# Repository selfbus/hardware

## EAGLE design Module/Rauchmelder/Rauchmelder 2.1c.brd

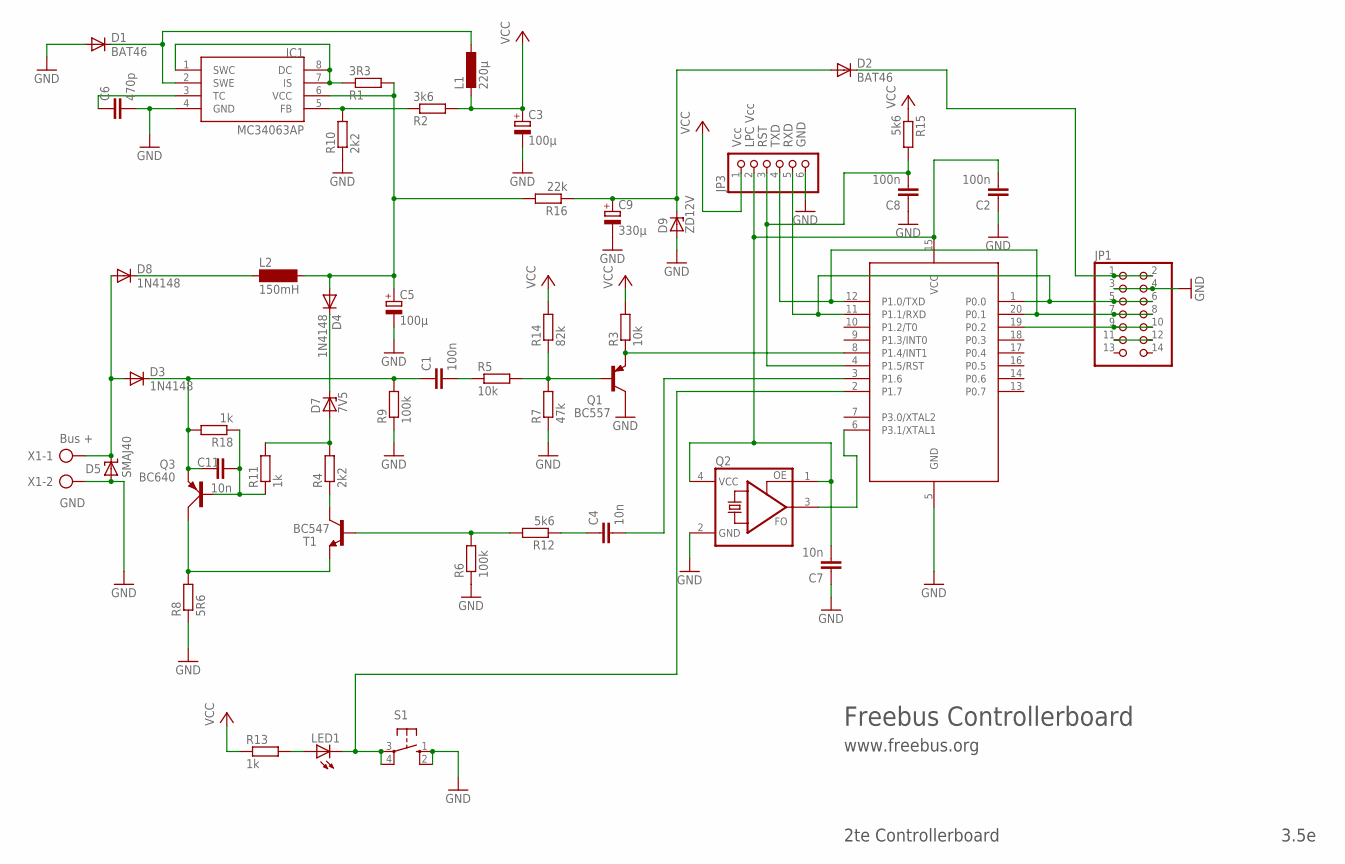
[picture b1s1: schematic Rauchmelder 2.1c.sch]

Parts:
89LPC922: 89LPC922; DIL20
C1, C2, C8: 100n; C025-024X044
C3: 100µ; E2,5-6
C4, C11: 10n; C025-024X044
C5: 100µ; E3,5-8
C6: 470p; C025-024X044
C7: 10n; C1206
C9: 330µ; E3,5-8
D1, D2: BAT46; DO34-7
D3, D4: 1N4148; DO35-10
D5: SMAJ40; SMBJ
D7: 7V5; ZDIO-2.5
D8: 1N4148; D-7.5
D9: ZD12V; DO34Z7
IC1: MC34063AP; DIL08
JP1: PINHD-2X7; 2X07
JP3: PINHD-1X6; 1X06
L1: 220µ; 0207/12
L2: 150mH; BS11
LED1: LED3MM
Q1: BC557; TO92
Q2: ASFL; ASF
Q3: BC640; SOT54D
R1: 3R3; 0207/7
R2: 3k6; 0207/7
R3, R5: 10k; 0207/7
R4: 2k2; 0207/2V
R6: 100k; 0207/2V
R7: 47k; 0207/7
R8: 5R6; 0207/2V
R9: 100k; 0207/7
R10: 2k2; 0207/7
R11, R18: 1k; 0207/2V
R12: 5k6; 0207/7
R13: 1k; 0207/7
R14: 82k; 0207/7
R15: 5k6; 0207/2V
R16: 22k; 0207/2V
S1: 10-XX; B3F-10XX
T1: BC547; TO92
X1: AK500/2

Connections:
EIB+: D3.A, D5.C, D8.A, X1.1
GND: 89LPC922.5 (GND), C2.1, C3.-, C5.-, C6.2, C7.1, C8.1, C9.-, D1.A, D5.A, D9.A, IC1.4 (GND), JP1.3, JP1.4, JP3.6, Q1.3 (C), Q2.2 (GND), R6.1, R7.1, R8.1, R9.1, R10.1, S1.1 (S), S1.2 (S1), X1.2
unnamed: 89LPC922.8 (P1.4/INT1), Q1.1 (E), R3.1
unnamed: Q1.2 (B), R5.2, R7.2, R14.1
unnamed: 89LPC922.6 (P3.1/XTAL1), Q2.3 (FO)
unnamed: C11.2, Q3.B, R11.1, R18.1
unnamed: 89LPC922.3 (P1.6), C4.2
unnamed: 89LPC922.15 (VCC), C2.2, C7.2, JP3.2, Q2.1 (OE), Q2.4 (VCC)
unnamed: 89LPC922.2 (P1.7), LED1.K (C), S1.3, S1.4 (P1)
unnamed: IC1.1 (SWC), IC1.7 (IS), IC1.8 (DC), R1.1
unnamed: LED1.A, R13.2
unnamed: C9.+, D2.A, D9.C, R16.1
unnamed: IC1.5 (FB), R2.1, R10.2
unnamed: D1.C, IC1.2 (SWE), L1.1
unnamed: D8.C, L2.1
unnamed: C6.1, IC1.3 (TC)
unnamed: D4.C, D7.C
unnamed: C1.2, R5.1
unnamed: C5.+, D4.A, IC1.6 (VCC), L2.2, R1.2, R16.2
unnamed: D2.C, JP1.1, JP1.2
unnamed: 89LPC922.4 (P1.5/RST), C8.2, JP3.3, R15.2
unnamed: 89LPC922.19 (P0.2), JP1.9, JP1.10
unnamed: C4.1, R12.1
unnamed: R4.1, T1.3 (C)
unnamed: JP1.11, JP1.12
unnamed: D7.A, R4.2, R11.2
unnamed: Q3.C, R8.2, T1.1 (E)
unnamed: C1.1, C11.1, D3.C, Q3.E, R9.2, R18.2
unnamed: R6.2, R12.2, T1.2 (B)
RX: 89LPC922.1 (P0.0), 89LPC922.11 (P1.1/RXD), JP1.5, JP1.6, JP3.5
TX: 89LPC922.12 (P1.0/TXD), 89LPC922.20 (P0.1), JP1.7, JP1.8, JP3.4
VCC: C3.+, JP3.1, L1.2, R2.2, R3.2, R13.1, R14.2, R15.1

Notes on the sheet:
Bus +
GND
Vcc
LPC Vcc
RST
TXD
RXD
Freebus Controllerboard
www.freebus.org
2te Controllerboard
3.5e

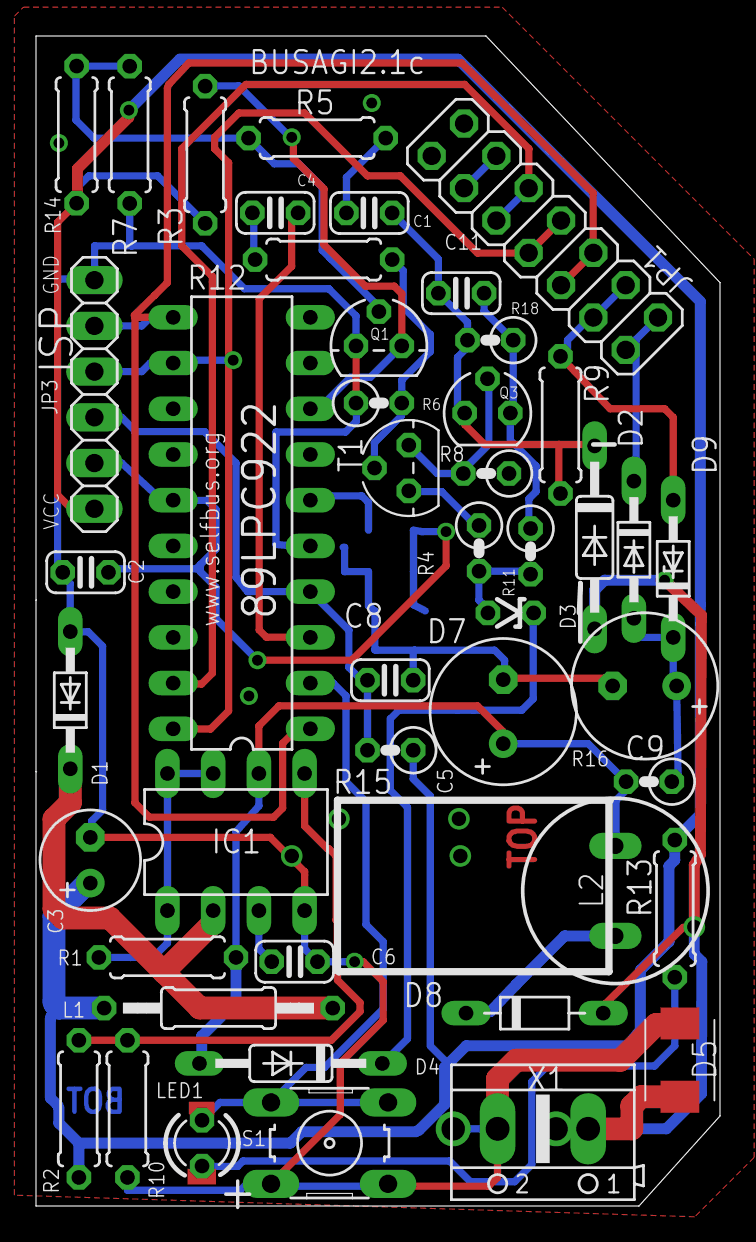
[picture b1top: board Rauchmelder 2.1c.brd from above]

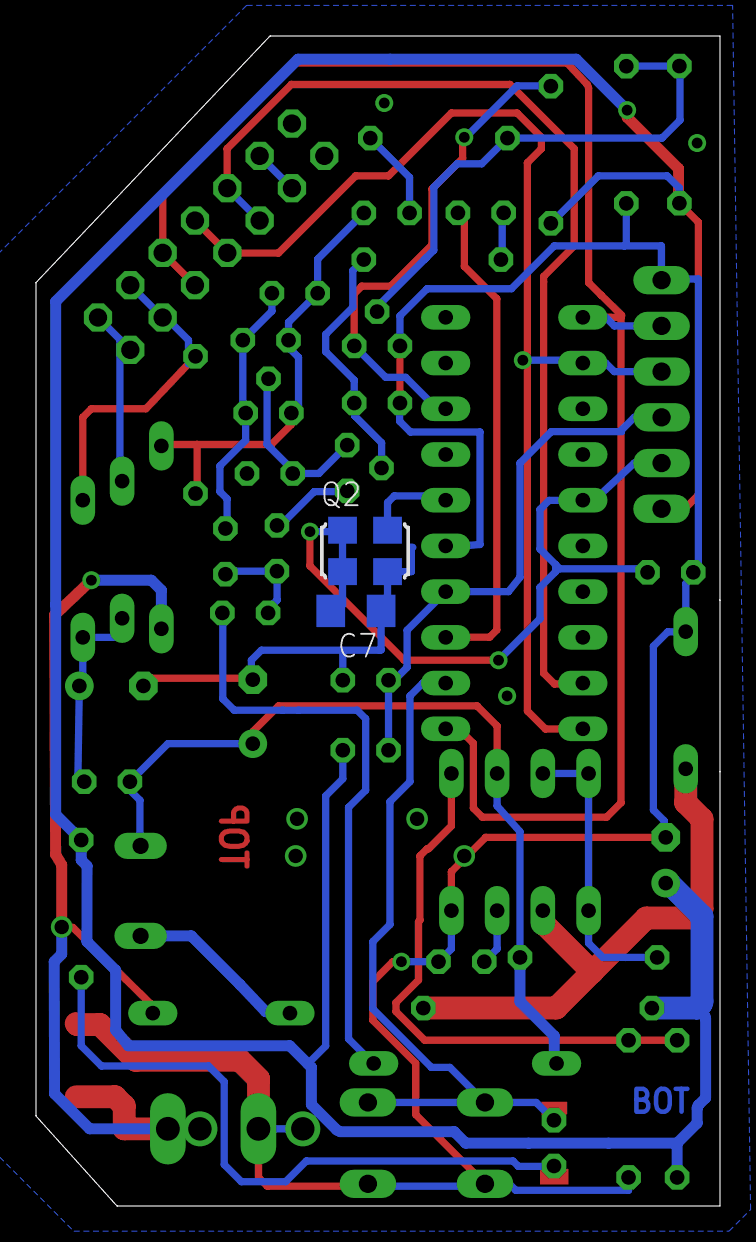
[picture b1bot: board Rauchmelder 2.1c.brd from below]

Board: 2 copper layers, 38.0 x 65.0 mm, 48 parts (2 on the bottom side), 32 nets.

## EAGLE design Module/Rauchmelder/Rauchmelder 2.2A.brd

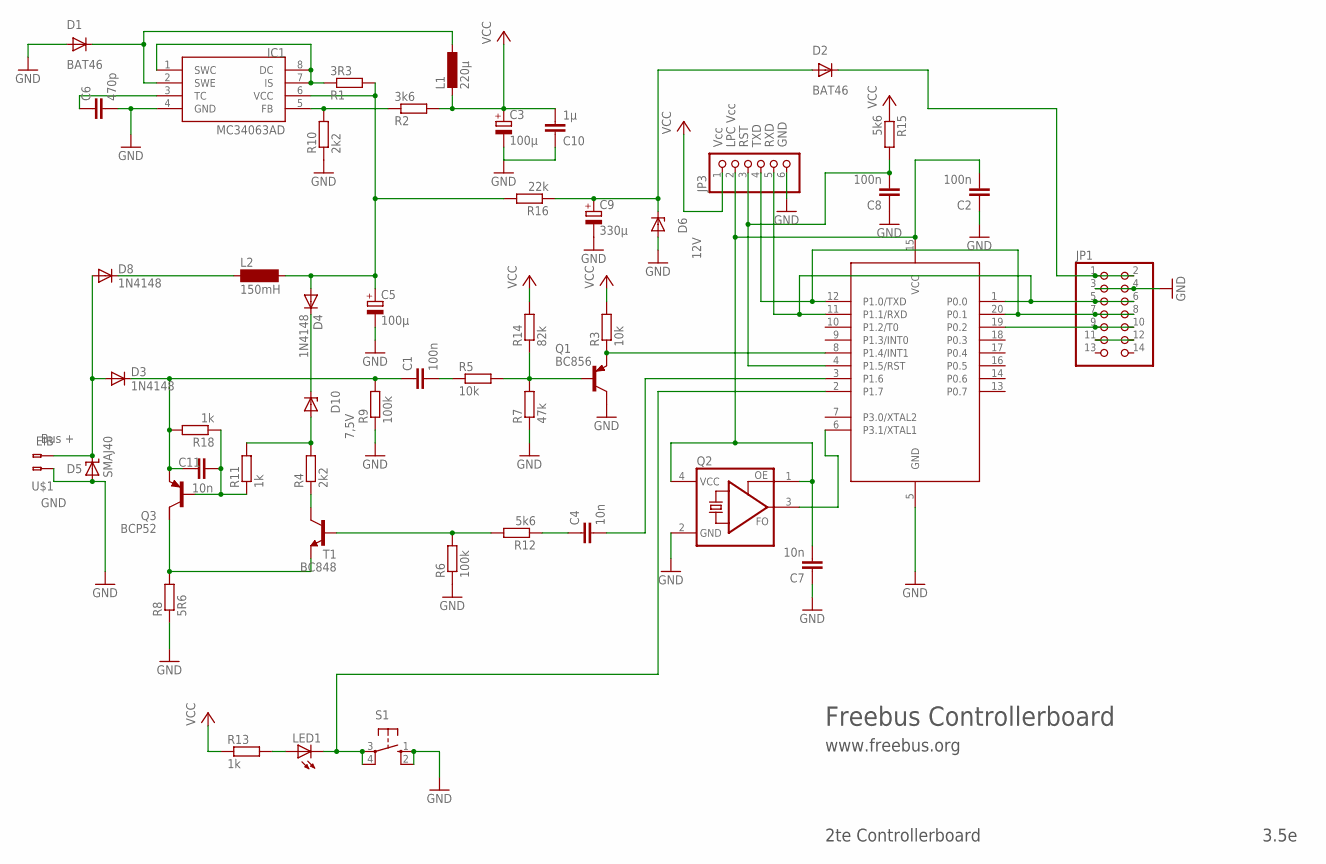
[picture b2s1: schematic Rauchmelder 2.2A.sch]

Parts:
C1, C2, C8: 100n; C1206
C3: 100µ; SANYO-OSCON_SMD_B6
C4, C7, C11: 10n; C1206
C5: 100µ; SANYO-OSCON_SMD_C6
C6: 470p; C1206
C9: 330µ; E3,5-8
C10: 1µ; C1206
D1, D2: BAT46; MINIMELF
D3, D4, D8: 1N4148; MINIMELF
D5: SMAJ40; SMBJ
D6: 12V; MINIMELF
D10: 7,5V; MINIMELF
IC1: MC34063AD; SOIC8
IC3: LPC922FDH; TSSOP20
JP1: PINHD-2X7; 2X07
JP3: PINHD-1X6; 1X06
L1: 220µ; 0207/10
L2: 150mH; BS11
LED1: LED3MM
Q1: BC856; SOT23-BEC
Q2: ASFL; ASF
Q3: BCP52; SOT223
R1: 3R3; R1206
R2: 3k6; R1206
R3, R5: 10k; R1206
R4, R10: 2k2; R1206
R6, R9: 100k; R1206
R7: 47k; R1206
R8: 5R6; R1206
R11, R13, R18: 1k; R1206
R12, R15: 5k6; R1206
R14: 82k; R1206
R16: 22k; R1206
S1: 10-XX; B3F-10XX
T1: BC848; SOT23
U$1: EIB; BUSKLEMME243-724

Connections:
EIB+: D3.A, D5.C, D8.A, U$1.2 (B-2)
GND: C2.1, C3.-, C5.-, C6.2, C7.1, C8.1, C9.-, C10.1, D1.A, D5.A, D6.A, IC1.4 (GND), IC3.5 (GND), JP1.3, JP1.4, JP3.6, Q1.C, Q2.2 (GND), R6.1, R7.1, R8.1, R9.1, R10.1, S1.1 (S), S1.2 (S1), U$1.1 (B-1)
unnamed: IC3.8 (P1.4/INT1), Q1.E, R3.1
unnamed: Q1.B, R5.2, R7.2, R14.1
unnamed: IC3.6 (P3.1/XTAL1), Q2.3 (FO)
unnamed: C11.2, Q3.1 (B), R11.1, R18.1
unnamed: C4.2, IC3.3 (P1.6)
unnamed: C2.2, C7.2, IC3.15 (VCC), JP3.2, Q2.1 (OE), Q2.4 (VCC)
unnamed: IC3.2 (P1.7), LED1.K (C), S1.3, S1.4 (P1)
unnamed: IC1.1 (SWC), IC1.7 (IS), IC1.8 (DC), R1.1
unnamed: LED1.A, R13.2
unnamed: C9.+, D2.A, D6.C, R16.1
unnamed: IC1.5 (FB), R2.1, R10.2
unnamed: D1.C, IC1.2 (SWE), L1.1
unnamed: D8.C, L2.1
unnamed: C6.1, IC1.3 (TC)
unnamed: D4.C, D10.C
unnamed: C1.2, R5.1
unnamed: C5.+, D4.A, IC1.6 (VCC), L2.2, R1.2, R16.2
unnamed: D2.C, JP1.1, JP1.2
unnamed: C8.2, IC3.4 (P1.5/RST), JP3.3, R15.2
unnamed: IC3.19 (P0.2), JP1.9, JP1.10
unnamed: C4.1, R12.1
unnamed: R4.1, T1.3 (C)
unnamed: JP1.11, JP1.12
unnamed: D10.A, R4.2, R11.2
unnamed: Q3.2 (C), R8.2, T1.2 (E)
unnamed: C1.1, C11.1, D3.C, Q3.3 (E), R9.2, R18.2
unnamed: R6.2, R12.2, T1.1 (B)
RX: IC3.1 (P0.0), IC3.11 (P1.1/RXD), JP1.5, JP1.6, JP3.5
TX: IC3.12 (P1.0/TXD), IC3.20 (P0.1), JP1.7, JP1.8, JP3.4
VCC: C3.+, C10.2, JP3.1, L1.2, R2.2, R3.2, R13.1, R14.2, R15.1

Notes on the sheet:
Bus +
GND
Vcc
LPC Vcc
RST
TXD
RXD
Freebus Controllerboard
www.freebus.org
2te Controllerboard
3.5e

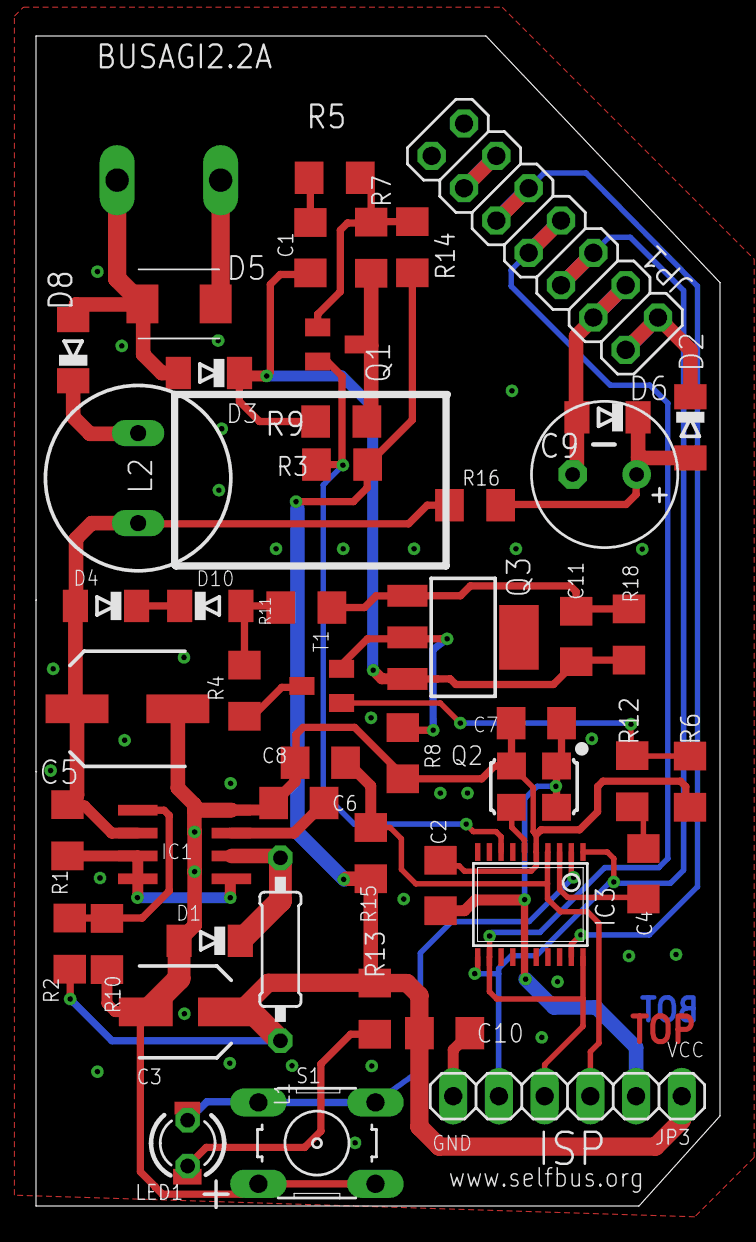
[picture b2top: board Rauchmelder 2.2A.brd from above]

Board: 2 copper layers, 38.0 x 65.0 mm, 49 parts (0 on the bottom side), 32 nets.
